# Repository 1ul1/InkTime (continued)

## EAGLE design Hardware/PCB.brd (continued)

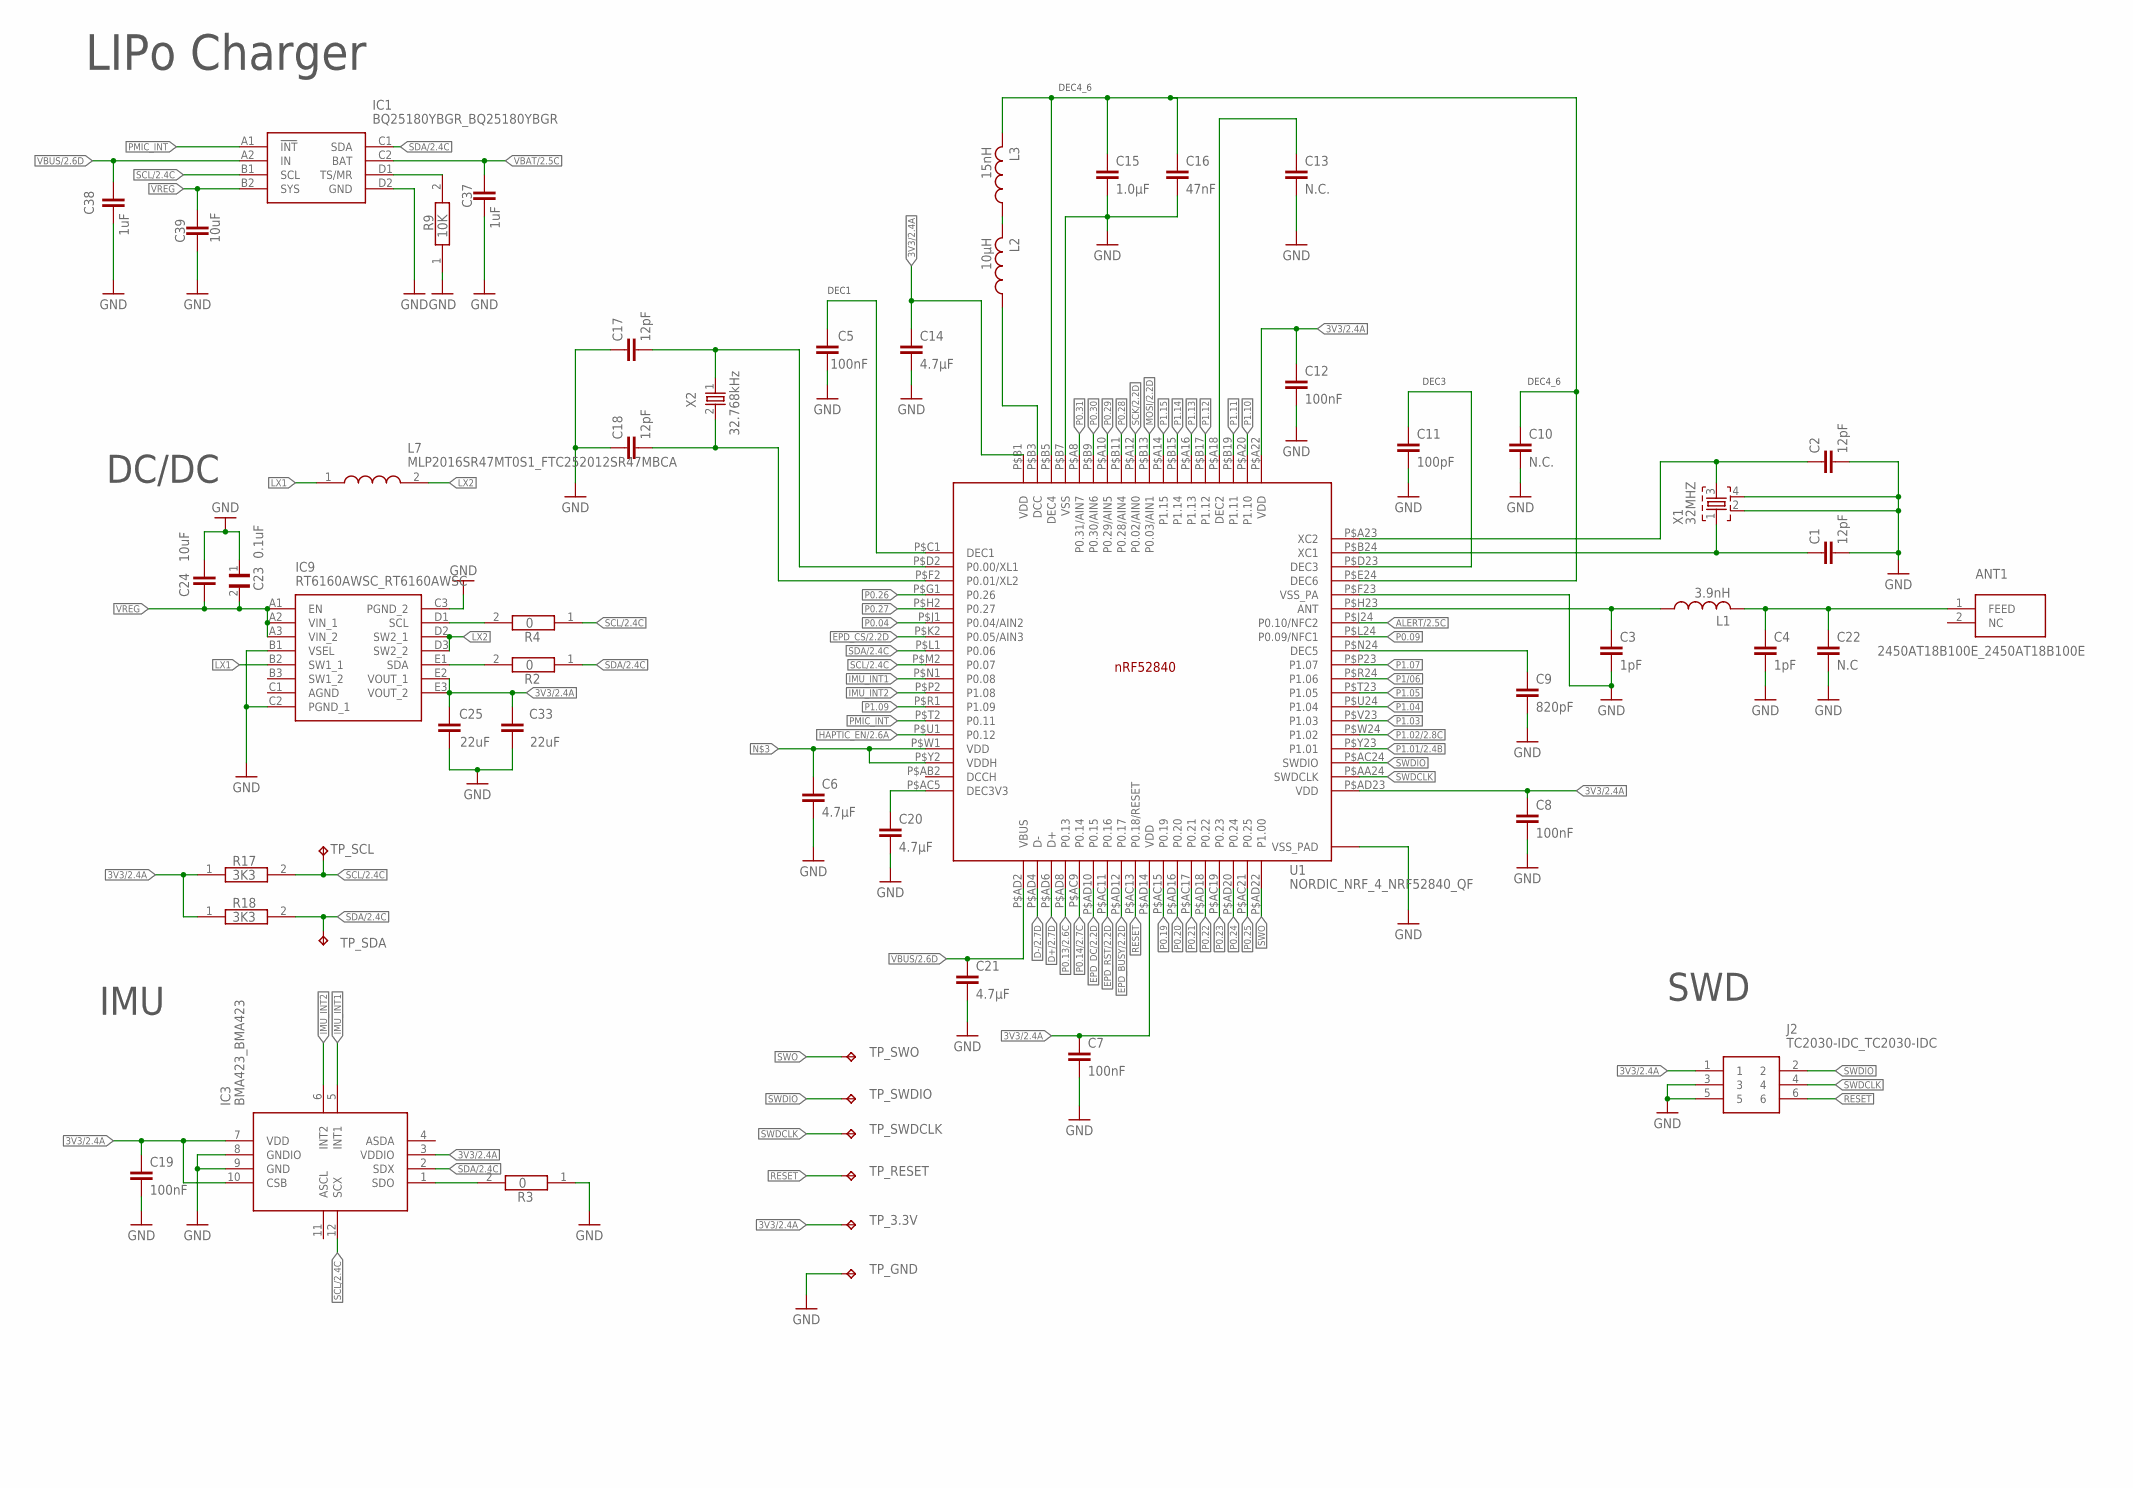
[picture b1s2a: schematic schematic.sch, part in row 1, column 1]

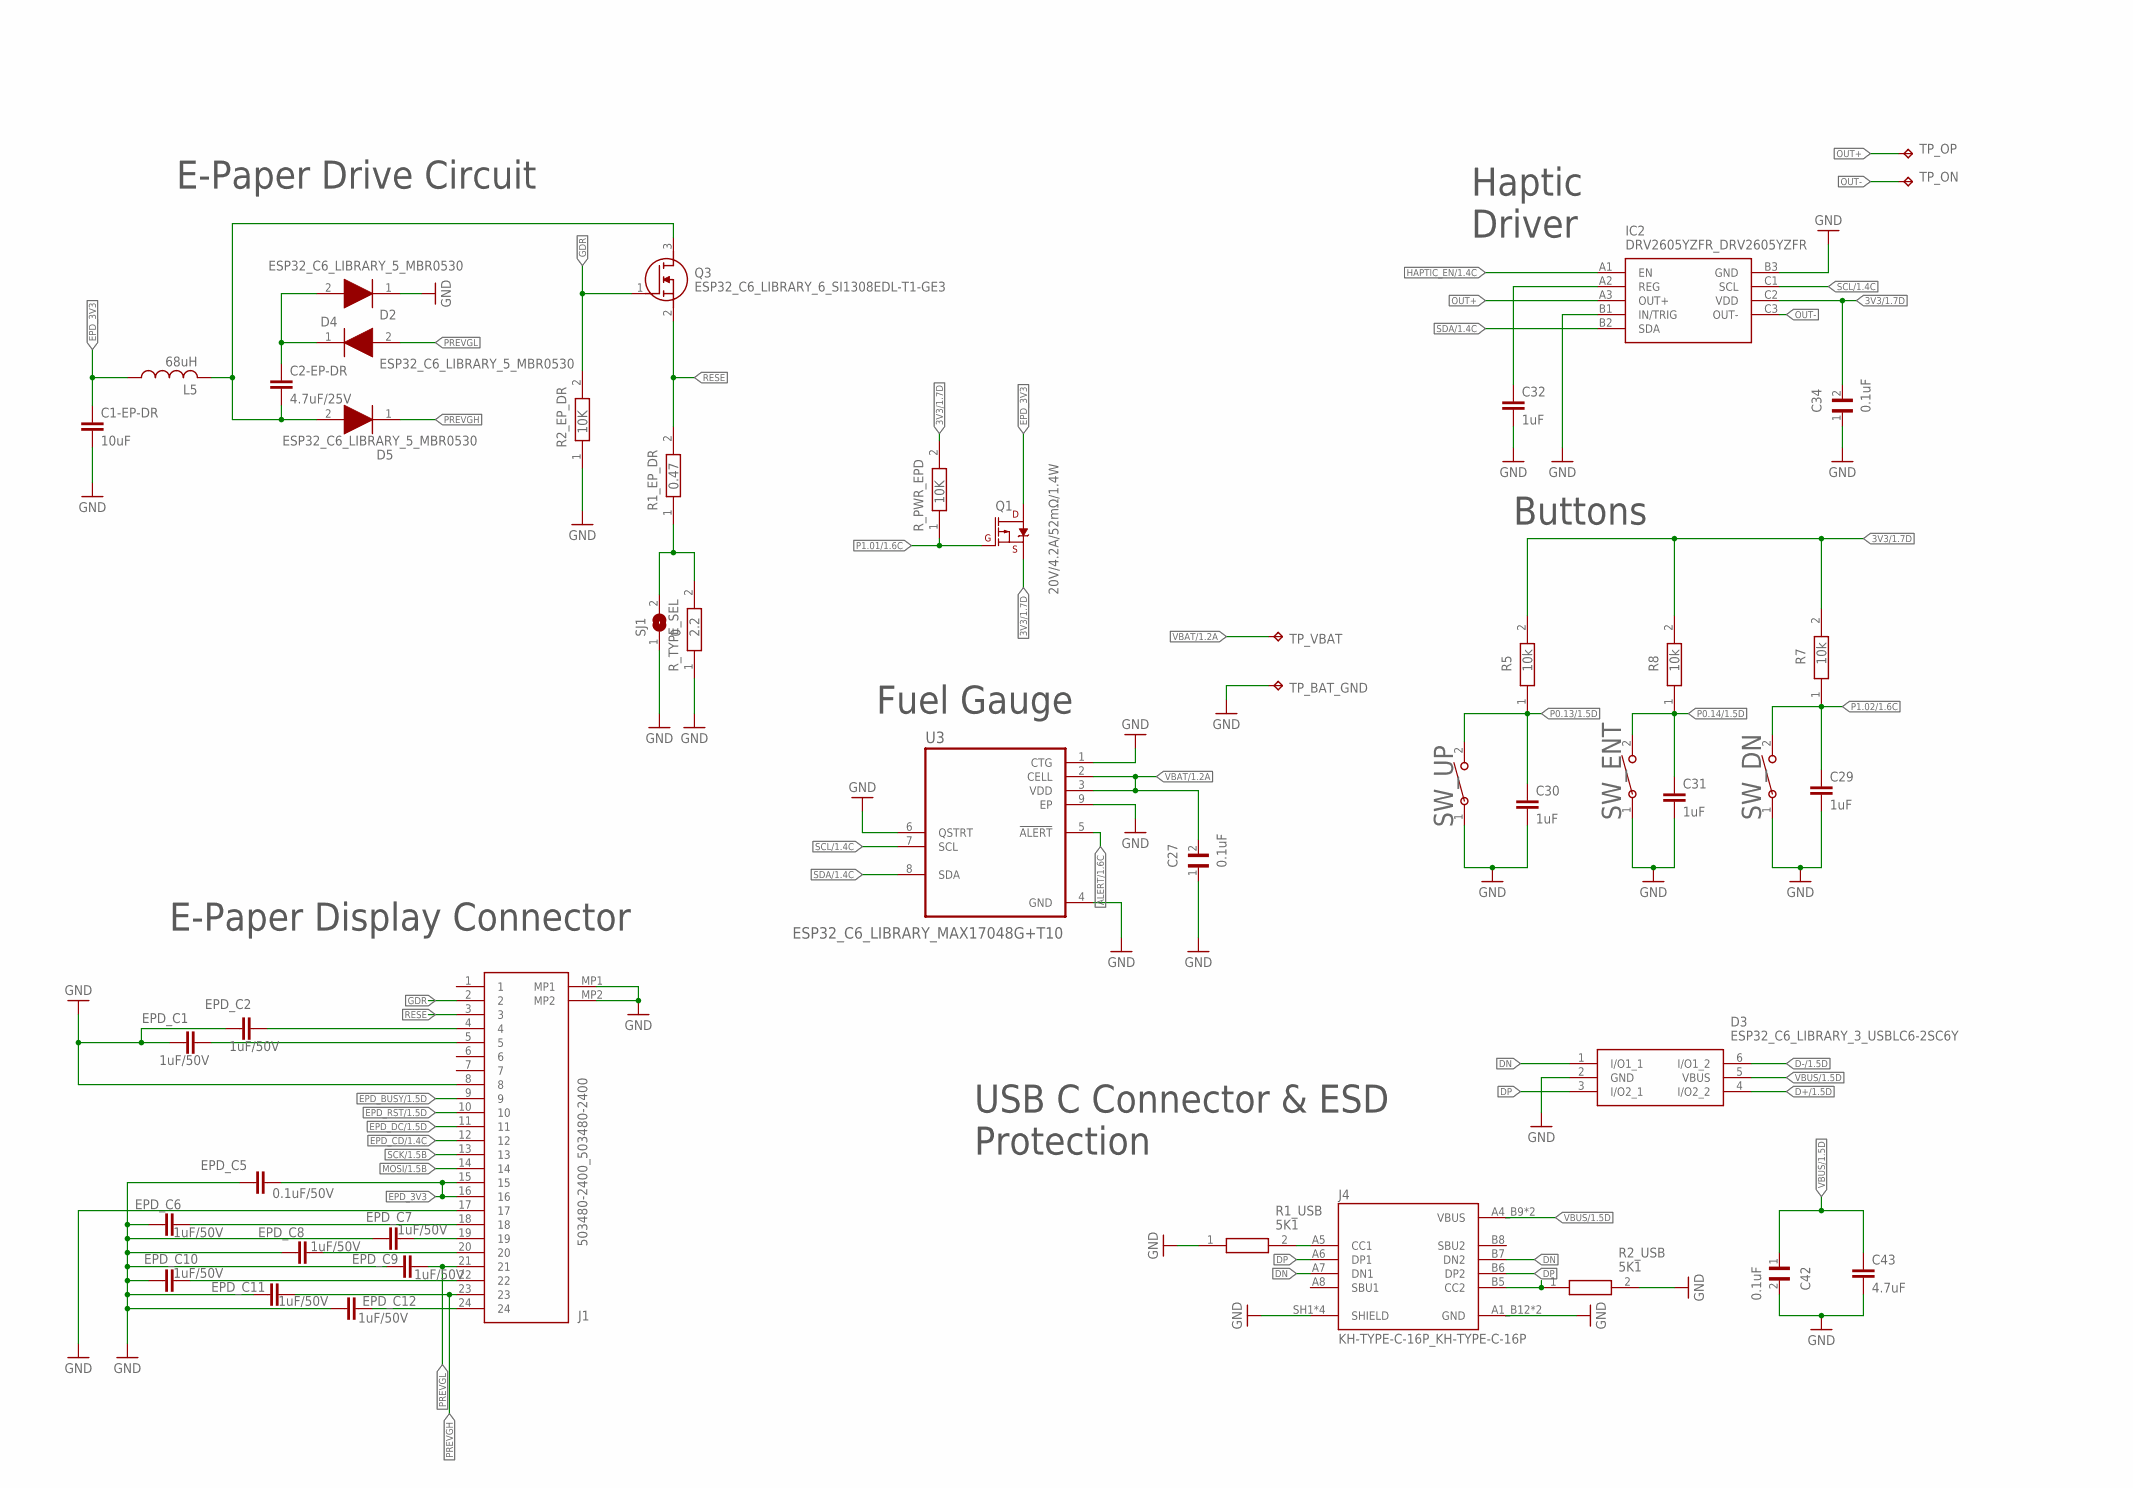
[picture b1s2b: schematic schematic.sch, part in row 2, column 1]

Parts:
ANT1: 2450AT18B100E_2450AT18B100E; 2450AT18B100E_ANTC3216X140N
C1, C2, C17, C18: 12pF; NORDIC_NRF_3_RESC0201_L
C1-EP-DR, C24, C39: 10uF; PERFECT_0402_0402
C2-EP-DR: 4.7uF/25V; PERFECT_0402_0402
C3, C4: 1pF; NORDIC_NRF_3_RESC0201_L
C5, C8, C12, C19: 100nF; NORDIC_NRF_3_RESC0201_L
C6, C14, C20, C21: 4.7µF; PERFECT_0402_0402
C7: 100nF; PERFECT_0402_0402
C9: 820pF; NORDIC_NRF_3_RESC0201_L
C10: N.C.; NORDIC_NRF_3_RESC0201_L
C11: 100pF; NORDIC_NRF_3_RESC0201_L
C13: N.C.; PERFECT_0402_0402
C15: 1.0µF; PERFECT_0402_0402
C16: 47nF; NORDIC_NRF_3_RESC0201_L
C22: N.C; NORDIC_NRF_3_RESC0201_L
C23, C27, C34, C42: 0.1uF; GRM011R60J152KE01L_2_CAPC0201X13N
C25, C33: 22uF; PERFECT_0402_0402
C29, C30, C31, C32, C37, C38: 1uF; PERFECT_0402_0402
C43: 4.7uF; PERFECT_0402_0402
D2, D4, D5: ESP32_C6_LIBRARY_5_MBR0530; ESP32_C6_LIBRARY_5_SOD3716X135N
D3: ESP32_C6_LIBRARY_3_USBLC6-2SC6Y; ESP32_C6_LIBRARY_3_SOT95P280X145-6N
EPD_C1, EPD_C2, EPD_C6, EPD_C7, EPD_C8, EPD_C9, EPD_C10, EPD_C11, EPD_C12: 1uF/50V; PERFECT_0402_0402
EPD_C5: 0.1uF/50V; NORDIC_NRF_3_RESC0201_L
IC1: BQ25180YBGR_BQ25180YBGR; BQ25180YBGR_BGA8C40P2X4_100X155X50
IC2: DRV2605YZFR_DRV2605YZFR; DRV2605YZFR_BGA9C50P3X3_144X144X62
IC3: BMA423_BMA423
IC9: RT6160AWSC_RT6160AWSC; RT6160AWSC_BGA15C40P3X5_140X230X60
J1: 503480-2400_503480-2400; 503480-2400_5034802400
J2: TC2030-IDC_TC2030-IDC; TC2030-IDC_TC2030IDC
J4: KH-TYPE-C-16P_KH-TYPE-C-16P; KH-TYPE-C-16P_KINGHELM_KH-TYPE-C-16P
L1: 3.9nH; NORDIC_NRF_2_RESC0402_L
L2: 10µH; NORDIC_NRF_2_RESC0402_L
L3: 15nH; NORDIC_NRF_2_RESC0402_L
L5: 68uH; NORDIC_NRF_2_RESC0402_L
L7: MLP2016SR47MT0S1_FTC252012SR47MBCA; MLP2016SR47MT0S1_INDC2016X100N
Q1: 20V/4.2A/52mΩ/1.4W; ESP32_C6_LIBRARY_4_ESP32_C6_LIBRARY_4_ESP32_C6_LIBRARY_4_ES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
Q3: ESP32_C6_LIBRARY_6_SI1308EDL-T1-GE3; ESP32_C6_LIBRARY_6_SOT65P210X110-3N
R1_EP_DR: 0.47; CPF0201D7K68C1_0201
R1_USB, R2_USB: 5K1; CPF0201D7K68C1_0201
R2, R3, R4: 0; ERA-1AEB3401C_0201
R2_EP_DR, R9: 10K; CPF0201D7K68C1_0201
R5, R7, R8: 10k; CPF0201D7K68C1_0201
R17, R18: 3K3; ERA-1AEB3401C_0201
R_PWR_EPD: 10K; CPF0201D7K68C1_0201
R_TYPE_SEL: 2.2; CPF0201D7K68C1_0201
SJ1: 0; ESP32_C6_LIBRARY_7_JUMPER_SJ
SW_DN: 2025-10-22_07-23-44_LIBRARY_EVP-AKE31ASW_EVP-AKE3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; 2025-10-22_07-23-44_LIBRARY_SW_EVP-AKE31A_PAN
SW_ENT: 2025-10-22_07-23-44_LIBRARY_EVP-AKE31ASW_EVP-AKE3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; 2025-10-22_07-23-44_LIBRARY_SW_EVP-AKE31A_PAN
SW_UP: 2025-10-22_07-23-44_LIBRARY_EVP-AKE31ASW_EVP-AKE3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; 2025-10-22_07-23-44_LIBRARY_SW_EVP-AKE31A_PAN
TP_3.3V: HECTOR_WATCH_1_TPTP20R; HECTOR_WATCH_1_TP20R
TP_BAT_GND: HECTOR_WATCH_1_TPTP20R; HECTOR_WATCH_1_TP20R
TP_GND: HECTOR_WATCH_1_TPTP20R; HECTOR_WATCH_1_TP20R
TP_ON: HECTOR_WATCH_1_TPTP20R; HECTOR_WATCH_1_TP20R
TP_OP: HECTOR_WATCH_1_TPTP20R; HECTOR_WATCH_1_TP20R
TP_RESET: HECTOR_WATCH_1_TPTP20R; HECTOR_WATCH_1_TP20R
TP_SCL: HECTOR_WATCH_1_TPTP20R; HECTOR_WATCH_1_TP20R
TP_SDA: HECTOR_WATCH_1_TPTP20R; HECTOR_WATCH_1_TP20R
TP_SWDCLK: HECTOR_WATCH_1_TPTP20R; HECTOR_WATCH_1_TP20R
TP_SWDIO: HECTOR_WATCH_1_TPTP20R; HECTOR_WATCH_1_TP20R
TP_SWO: HECTOR_WATCH_1_TPTP20R; HECTOR_WATCH_1_TP20R
TP_VBAT: HECTOR_WATCH_1_TPTP20R; HECTOR_WATCH_1_TP20R
U1: NORDIC_NRF_4_NRF52840_QF; NORDIC_NRF_4_AQFN50P700X700X85_HS-74N
U3: ESP32_C6_LIBRARY_MAX17048G+T10; ESP32_C6_LIBRARY_SON50P200X200X80-9N
X1: 32MHZ; NORDIC_NRF_BT-XTAL_2016_N
X2: 32.768kHz; NORDIC_NRF_1_XTAL_3215_N

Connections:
3V3/1.7D: C34.2, IC2.C2 (VDD), Q1.2 (S), R5.2, R7.2, R8.2, R_PWR_EPD.2
3V3/2.4A: C7.1, C8.1, C12.1, C14.1, C19.1, C25.2, C33.2, IC3.3 (VDDIO), IC3.7 (VDD), IC3.10 (CSB), IC9.E2 (VOUT_1), IC9.E3 (VOUT_2), J2.1, R17.1, R18.1, TP_3.3V.TP, U1.P$A22 (VDD), U1.P$AD14 (VDD), U1.P$AD23 (VDD), U1.P$B1 (VDD)
ALERT/1.6C: U3.5 (!ALERT)
ALERT/2.5C: U1.P$J24 (P0.10/NFC2)
D+/1.5D: D3.4 (I/O2_2)
D+/2.7D: U1.P$AD6 (D+)
D-/1.5D: D3.6 (I/O1_2)
D-/2.7D: U1.P$AD4 (D-)
DN: D3.1 (I/O1_1), J4.A7 (DN1), J4.B7 (DN2)
DP: D3.3 (I/O2_1), J4.A6 (DP1), J4.B6 (DP2)
EPD_3V3: C1-EP-DR.1, EPD_C5.2, J1.15, J1.16, L5.1, Q1.3 (D)
EPD_BUSY/1.5D: J1.9
EPD_BUSY/2.2D: U1.P$AC11 (P0.16)
EPD_CD/1.4C: J1.12
EPD_CS/2.2D: U1.P$K2 (P0.05/AIN3)
EPD_DC/1.5D: J1.11
EPD_DC/2.2D: U1.P$AD10 (P0.15)
EPD_RST/1.5D: J1.10
EPD_RST/2.2D: U1.P$AD12 (P0.17)
GDR: J1.2, Q3.1 (G), R2_EP_DR.2
GND: C1.2, C1-EP-DR.2, C2.2, C3.2, C4.2, C5.1, C6.2, C7.2, C8.2, C9.2, C10.2, C11.2, C12.2, C13.2, C14.2, C15.2, C16.2, C17.1, C18.1, C19.2, C20.2, C21.2, C22.2, C23.1, C24.2, C25.1, C27.1, C29.2, C30.2, C31.2, C32.2, C33.1, C34.1, C37.2, C38.2, C39.2, C42.2, C43.2, D3.2 (GND), D4.1 (K), EPD_C1.1, EPD_C2.1, EPD_C5.1, EPD_C6.1, EPD_C7.1, EPD_C8.1, EPD_C9.1, EPD_C10.1, EPD_C11.1, EPD_C12.1, IC1.D2 (GND), IC2.B1 (IN/TRIG), IC2.B3 (GND), IC3.8 (GNDIO), IC3.9 (GND), IC9.B1 (VSEL), IC9.C2 (PGND_1), IC9.C3 (PGND_2), J1.8, J1.17, J1.MP1, J1.MP2, J2.3, J2.5, J4.A1_B12 (GND), J4.A12_B1 (GND), J4.SH1 (SHIELD), J4.SH2 (SHIELD), J4.SH3 (SHIELD), J4.SH4 (SHIELD), R1_USB.1, R2_EP_DR.1, R2_USB.2, R3.1, R9.1, R_TYPE_SEL.1, SJ1.1, SW_DN.1, SW_ENT.1, SW_UP.1, TP_BAT_GND.TP, TP_GND.TP, U1.P$74 (VSS_PAD), U1.P$75 (VSS_PAD), U1.P$76 (VSS_PAD), U1.P$77 (VSS_PAD), U1.P$78 (VSS_PAD), U1.P$79 (VSS_PAD), U1.P$80 (VSS_PAD), U1.P$81 (VSS_PAD), U1.P$82 (VSS_PAD), U1.P$83 (VSS_PAD), U1.P$84 (VSS_PAD), U1.P$85 (VSS_PAD), U1.P$86 (VSS_PAD), U1.P$87 (VSS_PAD), U1.P$88 (VSS_PAD), U1.P$89 (VSS_PAD), U1.P$90 (VSS_PAD), U1.P$B7 (VSS), U1.P$F23 (VSS_PA), U3.1 (CTG), U3.4 (GND), U3.6 (QSTRT), U3.9 (EP), X1.2, X1.4
HAPTIC_EN/1.4C: IC2.A1 (EN)
HAPTIC_EN/2.6A: U1.P$U1 (P0.12)
IMU_INT1: IC3.5 (INT1), U1.P$N1 (P0.08)
IMU_INT2: IC3.6 (INT2), U1.P$P2 (P1.08)
LX1: IC9.B2 (SW1_1), L7.1
LX2: IC9.D2 (SW2_1), IC9.D3 (SW2_2), L7.2
MOSI/1.5B: J1.14
MOSI/2.2D: U1.P$B13 (P0.03/AIN1)
unnamed: IC3.1 (SDO), R3.2
unnamed: C20.1, U1.P$AC5 (DEC3V3)
unnamed: C6.1, U1.P$W1 (VDD), U1.P$Y2 (VDDH)
unnamed: C18.2, U1.P$F2 (P0.01/XL2), X2.2
unnamed: C17.2, U1.P$D2 (P0.00/XL1), X2.1
unnamed: C5.2, U1.P$C1 (DEC1)
unnamed: L2.2, L3.1
unnamed: IC1.D1 (TS/MR), R9.2
unnamed: IC9.D1 (SCL), R4.2
unnamed: IC9.E1 (SDA), R2.2
unnamed: L2.1, U1.P$B3 (DCC)
unnamed: C3.1, L1.1, U1.P$H23 (ANT)
unnamed: C13.1, U1.P$A18 (DEC2)
unnamed: C10.1, C15.1, C16.1, L3.2, U1.P$B5 (DEC4), U1.P$E24 (DEC6)
unnamed: C9.1, U1.P$N24 (DEC5)
unnamed: C1.1, U1.P$B24 (XC1), X1.1
unnamed: C11.1, U1.P$D23 (DEC3)
unnamed: C2.1, U1.P$A23 (XC2), X1.3
unnamed: ANT1.1 (FEED), C4.1, C22.1, L1.2
unnamed: J4.A5 (CC1), R1_USB.2
unnamed: C2-EP-DR.2, D5.2 (A), L5.2, Q3.3 (D)
unnamed: C2-EP-DR.1, D2.1 (K), D4.2 (A)
unnamed: C32.1, IC2.A2 (REG)
unnamed: R1_EP_DR.1, R_TYPE_SEL.2, SJ1.2
unnamed: EPD_C2.2, J1.4
unnamed: EPD_C1.2, J1.5
unnamed: J4.B5 (CC2), R2_USB.1
unnamed: EPD_C12.2, J1.24
unnamed: EPD_C10.2, J1.22
unnamed: EPD_C8.2, J1.20
unnamed: EPD_C7.2, J1.19
unnamed: EPD_C6.2, J1.18
OUT+: IC2.A3 (OUT+), TP_OP.TP
OUT-: IC2.C3 (OUT-), TP_ON.TP
P0.04: U1.P$J1 (P0.04/AIN2)
P0.09: U1.P$L24 (P0.09/NFC1)
P0.13/1.5D: C30.1, R5.1, SW_UP.2
P0.13/2.6C: U1.P$AD8 (P0.13)
P0.14/1.5D: C31.1, R8.1, SW_ENT.2
P0.14/2.7C: U1.P$AC9 (P0.14)
P0.19: U1.P$AC15 (P0.19)
P0.20: U1.P$AD16 (P0.20)
P0.21: U1.P$AC17 (P0.21)
P0.22: U1.P$AD18 (P0.22)
P0.23: U1.P$AC19 (P0.23)
P0.24: U1.P$AD20 (P0.24)
P0.25: U1.P$AC21 (P0.25)
P0.26: U1.P$G1 (P0.26)
P0.27: U1.P$H2 (P0.27)
P0.28: U1.P$B11 (P0.28/AIN4)
P0.29: U1.P$A10 (P0.29/AIN5)
P0.30: U1.P$B9 (P0.30/AIN6)
P0.31: U1.P$A8 (P0.31/AIN7)
P1.01/1.6C: Q1.1 (G), R_PWR_EPD.1
P1.01/2.4B: U1.P$Y23 (P1.01)
P1.02/1.6C: C29.1, R7.1, SW_DN.2
P1.02/2.8C: U1.P$W24 (P1.02)
P1.03: U1.P$V23 (P1.03)
P1.04: U1.P$U24 (P1.04)
P1.05: U1.P$T23 (P1.05)
P1.07: U1.P$P23 (P1.07)
P1.09: U1.P$R1 (P1.09)
P1.10: U1.P$A20 (P1.10)
P1.11: U1.P$B19 (P1.11)
P1.12: U1.P$B17 (P1.12)
P1.13: U1.P$A16 (P1.13)
P1.14: U1.P$B15 (P1.14)
P1.15: U1.P$A14 (P1.15)
P1/06: U1.P$R24 (P1.06)
PMIC_INT: IC1.A1 (!INT), U1.P$T2 (P0.11)
PREVGH: D5.1 (K), EPD_C11.2, J1.23
PREVGL: D2.2 (A), EPD_C9.2, J1.21
RESE: J1.3, Q3.2 (S), R1_EP_DR.2
RESET: J2.6, TP_RESET.TP, U1.P$AC13 (P0.18/RESET)
SCK/1.5B: J1.13
SCK/2.2D: U1.P$A12 (P0.02/AIN0)
SCL/1.4C: IC2.C1 (SCL), U3.7 (SCL)
SCL/2.4C: IC1.B1 (SCL), IC3.12 (SCX), R4.1, R17.2, TP_SCL.TP, U1.P$M2 (P0.07)
SDA/1.4C: IC2.B2 (SDA), U3.8 (SDA)
SDA/2.4C: IC1.C1 (SDA), IC3.2 (SDX), R2.1, R18.2, TP_SDA.TP, U1.P$L1 (P0.06)
SWDCLK: J2.4, TP_SWDCLK.TP, U1.P$AA24 (SWDCLK)
SWDIO: J2.2, TP_SWDIO.TP, U1.P$AC24 (SWDIO)
SWO: TP_SWO.TP, U1.P$AD22 (P1.00)
VBAT/1.2A: C27.2, TP_VBAT.TP, U3.2 (CELL), U3.3 (VDD)
VBAT/2.5C: C37.1, IC1.C2 (BAT)
VBUS/1.5D: C42.1, C43.1, D3.5 (VBUS), J4.A4_B9 (VBUS), J4.A9_B4 (VBUS)
VBUS/2.6D: C21.1, C38.1, IC1.A2 (IN), U1.P$AD2 (VBUS)
VREG: C23.2, C24.1, C39.1, IC1.B2 (SYS), IC9.A1 (EN), IC9.A2 (VIN_1), IC9.A3 (VIN_2)

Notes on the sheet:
SWD
IMU
DEC1
DEC4_6
DEC3
LIPo Charger
DC/DC
E-Paper Drive Circuit
E-Paper Display Connector
Fuel Gauge
Buttons
Haptic Driver
USB C Connector & ESD Protection

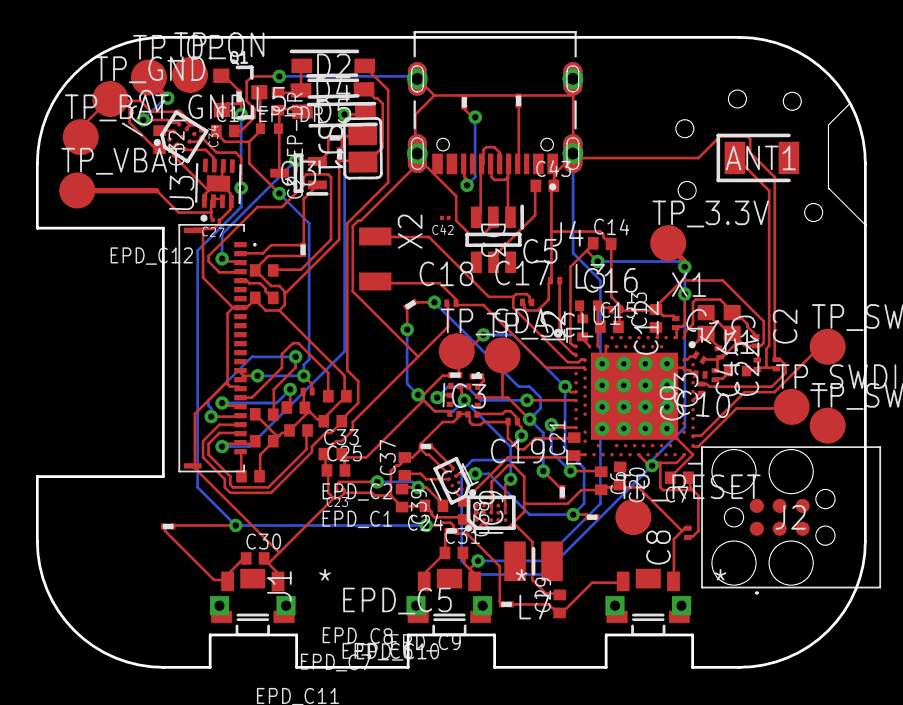
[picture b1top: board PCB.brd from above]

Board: 2 copper layers, 46.0 x 35.0 mm, 103 parts (0 on the bottom side), 66 nets.

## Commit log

2026-04-10 Initial Upload
2026-04-10 reupload
2026-04-10 + dir
